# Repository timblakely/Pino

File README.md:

# Pino

Pino the robot. An ongoing project to build a quadrupedal robot from the ground
up. 

## Disclaimer: this will not currently work for you.

This repository is a continuously changing, seething mess, and will continue to
be so for the forseeable future. I've made essentially zero effort to make this
work for anyone other than my own development environment, and the git commit
history is an absolute trainwreck. You're welcome to browse around the code, but
please don't expect anything to actually work without somewhat extensive removal
of the various hard-coded paths, hacks, and general terrible code health. If
you're still reading this and are actually interested in getting any of this to
_maybe_ compile, let me know via GitHub or my-github-username@gmail :)

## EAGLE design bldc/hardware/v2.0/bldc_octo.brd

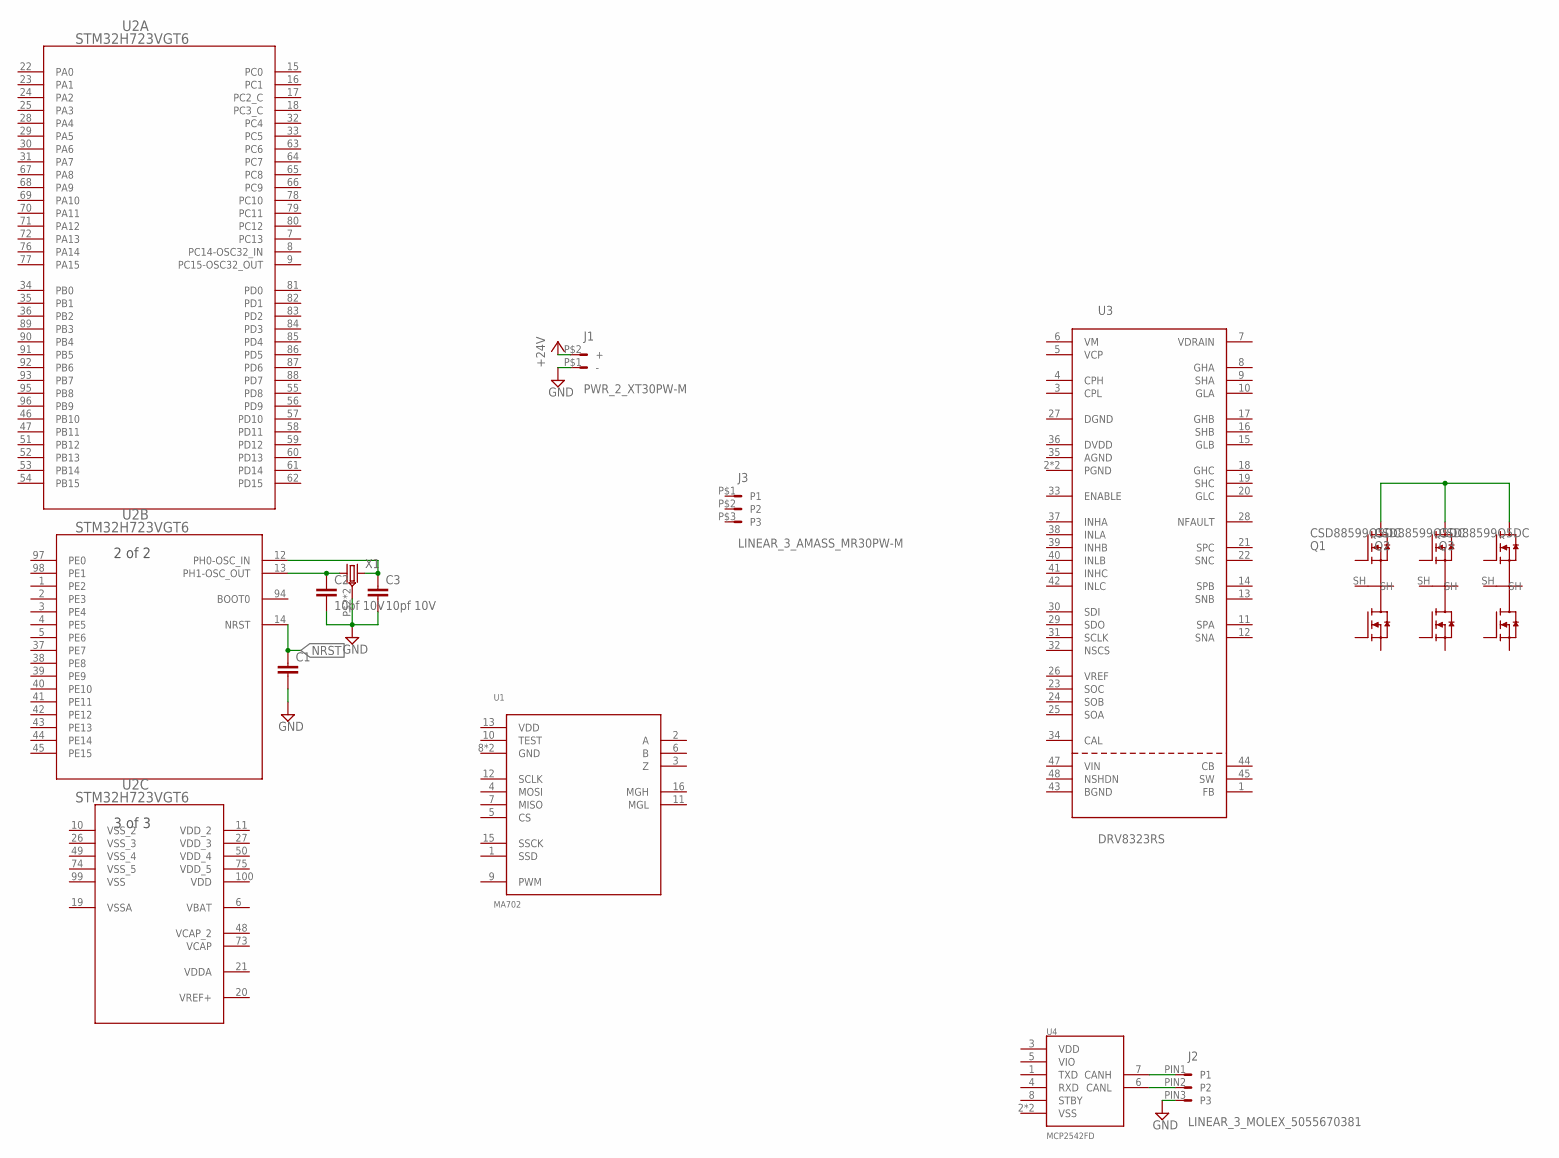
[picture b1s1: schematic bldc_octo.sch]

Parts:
C1: C0603
C2, C3: 10pf 10V; C0603
J1: PWR_2_XT30PW-M; XT30PW-M
J2: LINEAR_3_MOLEX_5055670381; MOLEX_5055670381
J3: LINEAR_3_AMASS_MR30PW-M; MR30PW-M
Q1, Q2, Q3: CSD88599Q5DC
U1: MA702; QFN-16_3X3
U2: STM32H723VGT6; LQFP100_STM
U3: DRV8323RS; VQFN-48_7X7
U4: MCP2542FD; TDFN_2X3
X1: CRYSTAL_NX2016SA-24MHZ-EXS00A-CS11335; NX201SA

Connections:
+24V: J1.P$2 (+)
GND: C1.2, C2.2, C3.2, J1.P$1 (-), J2.PIN3 (P3), X1.P$2 (GND), X1.P$4 (GND)
unnamed: J2.PIN1 (P1), U4.7 (CANH)
unnamed: J2.PIN2 (P2), U4.6 (CANL)
unnamed: C2.1, U2.13 (PH1-OSC_OUT), X1.P$1 (1)
unnamed: C3.1, U2.12 (PH0-OSC_IN), X1.P$3 (2)
unnamed: Q1.VIN$1 (V_IN), Q1.VIN$2 (V_IN), Q1.VIN$3 (V_IN), Q1.VIN$4 (V_IN), Q1.VIN$5 (V_IN), Q1.VIN$6 (V_IN), Q1.VIN$7 (V_IN), Q1.VIN$8 (V_IN), Q1.VIN$9 (V_IN), Q1.VIN$10 (V_IN), Q1.VIN$11 (V_IN), Q2.VIN$1 (V_IN), Q2.VIN$2 (V_IN), Q2.VIN$3 (V_IN), Q2.VIN$4 (V_IN), Q2.VIN$5 (V_IN), Q2.VIN$6 (V_IN), Q2.VIN$7 (V_IN), Q2.VIN$8 (V_IN), Q2.VIN$9 (V_IN), Q2.VIN$10 (V_IN), Q2.VIN$11 (V_IN), Q3.VIN$1 (V_IN), Q3.VIN$2 (V_IN), Q3.VIN$3 (V_IN), Q3.VIN$4 (V_IN), Q3.VIN$5 (V_IN), Q3.VIN$6 (V_IN), Q3.VIN$7 (V_IN), Q3.VIN$8 (V_IN), Q3.VIN$9 (V_IN), Q3.VIN$10 (V_IN), Q3.VIN$11 (V_IN)
NRST: C1.1, U2.14 (NRST)
VBAT: U2.6 (VBAT)
VCAP: U2.73 (VCAP)
VCAP_2: U2.48 (VCAP_2)
VDD: U2.100 (VDD)
VDDA: U2.21 (VDDA)
VDD_2: U2.11 (VDD_2)
VDD_3: U2.27 (VDD_3)
VDD_4: U2.50 (VDD_4)
VDD_5: U2.75 (VDD_5)
VREF+: U2.20 (VREF+)
VSS: U2.99 (VSS)
VSSA: U2.19 (VSSA)
VSS_2: U2.10 (VSS_2)
VSS_3: U2.26 (VSS_3)
VSS_4: U2.49 (VSS_4)
VSS_5: U2.74 (VSS_5)

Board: 4 copper layers, 14 parts (5 on the bottom side), 7 nets, no tracks yet.

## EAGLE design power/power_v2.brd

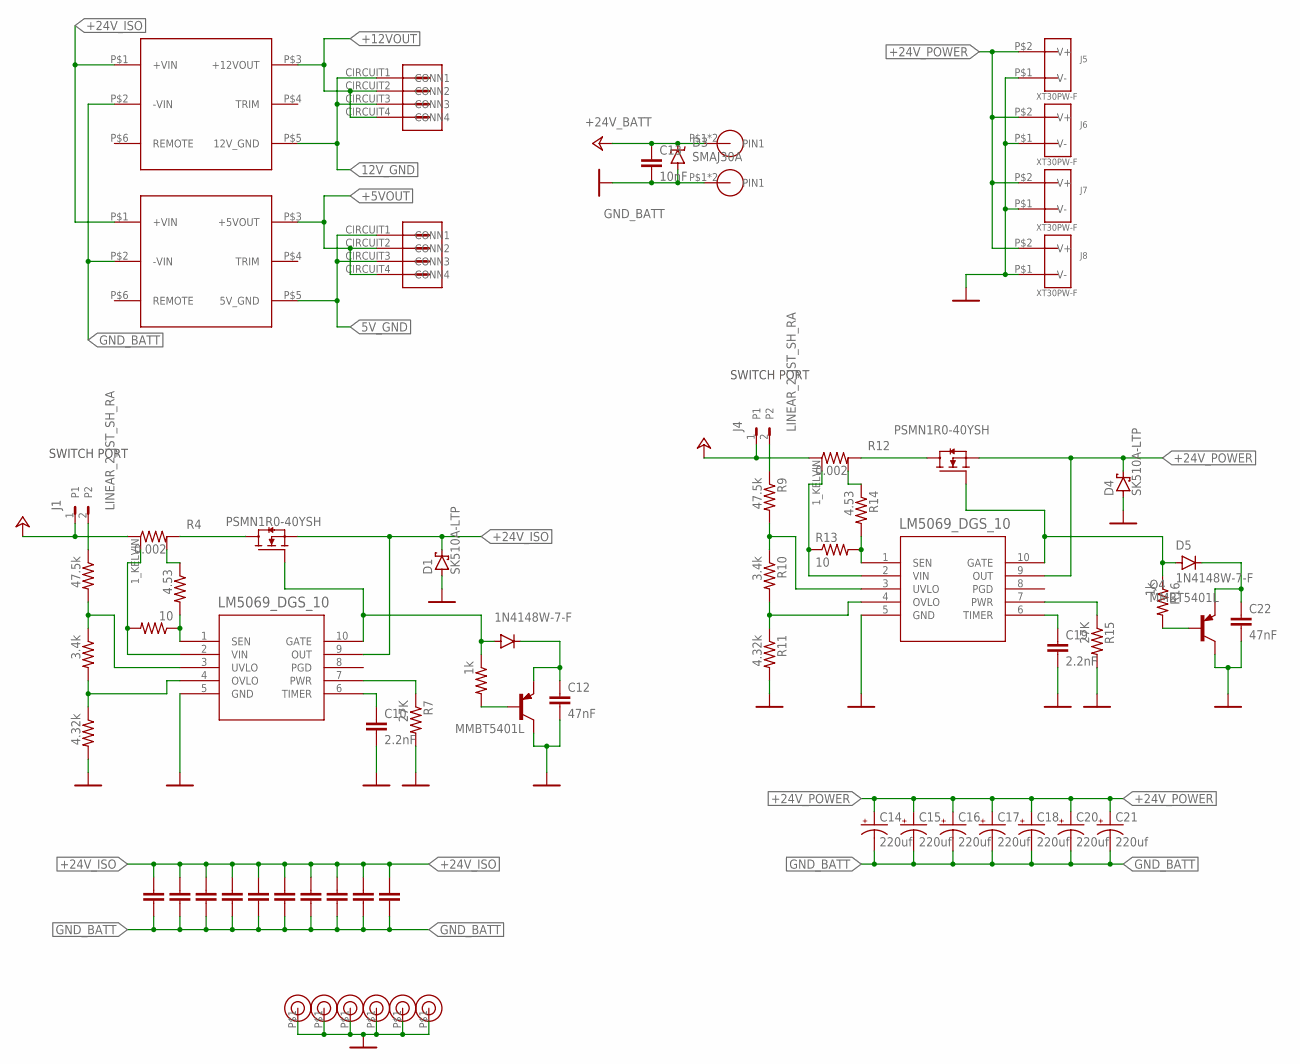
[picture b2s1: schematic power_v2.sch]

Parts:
C1: 2.2nF; C1210
C2, C3, C4, C5, C6, C7, C8, C9, C11: 10uF; C1210
C10, C19: 2.2nF; C0603
C12, C22: 47nF; C0603
C13: 10nF; C0603
C14, C15, C16, C17, C18, C20, C21: 220uf; C_ELEC_8X11_5
D1, D4: SK510A-LTP; DO-214AC
D2, D5: 1N4148W-7-F; SOD123
D3: SMAJ30A; DO-214AC
H1, H2, H3, H4, H5, H6: GND_HOLE_M3; HOLE_GND_M3
J1, J4: LINEAR_2_JST_SH_RA; JST_SM02B-SRSS-TB
J2: 12v; MOLEX_4_RA
J3: 5v; MOLEX_4_RA
J5, J6, J7, J8: XT30PW-F
P1, P2: FASTON1289_ST; FASTON_1289-ST
PS3: PDQ30-Q24-S12-D; PDQ30-D
PS4: PDQ30-Q24-S5-D; PDQ30-D
Q1, Q3: PSMN1R0-40YSH; LFPAK56E
Q2, Q4: MMBT5401L; SOT23-3
R1, R9: 47.5k; R0603
R2, R10: 3.4k; R0603
R3, R11: 4.32k; R0603
R4, R12: 0.002; R1210_KELVIN
R5, R13: 10; R0603
R6, R14: 4.53; R0603
R7, R15: 27K; R0603
R8, R16: 1k; R0603
U1, U2: LM5069_DGS_10; VSSOP_DGS_10

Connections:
5V_GND: J3.CIRCUIT1 (CONN1), J3.CIRCUIT3 (CONN3), PS4.P$5 (5V_GND)
12V_GND: J2.CIRCUIT1 (CONN1), J2.CIRCUIT3 (CONN3), PS3.P$5 (12V_GND)
+5VOUT: J3.CIRCUIT2 (CONN2), J3.CIRCUIT4 (CONN4), PS4.P$3 (+5VOUT)
+12VOUT: J2.CIRCUIT2 (CONN2), J2.CIRCUIT4 (CONN4), PS3.P$3 (+12VOUT)
+24V_BATT: C13.1, D3.C, J1.1, J4.1, P1.P$1, P1.P$2, R4.1A (1), R4.1B (1), R12.1A (1), R12.1B (1)
+24V_ISO: C1.1, C2.1, C3.1, C4.1, C5.1, C6.1, C7.1, C8.1, C9.1, C11.1, D1.C, PS3.P$1 (+VIN), PS4.P$1 (+VIN), Q1.1 (S), Q1.2 (S), Q1.3 (S), U1.9 (OUT)
+24V_POWER: C14.1 (+), C15.1 (+), C16.1 (+), C17.1 (+), C18.1 (+), C20.1 (+), C21.1 (+), D4.C, J5.P$2 (V+), J6.P$2 (V+), J7.P$2 (V+), J8.P$2 (V+), Q3.1 (S), Q3.2 (S), Q3.3 (S), U2.9 (OUT)
GND_BATT: C1.2, C2.2, C3.2, C4.2, C5.2, C6.2, C7.2, C8.2, C9.2, C10.2, C11.2, C12.2, C13.2, C14.2 (-), C15.2 (-), C16.2 (-), C17.2 (-), C18.2 (-), C19.2, C20.2 (-), C21.2 (-), C22.2, D1.A, D3.A, D4.A, H1.P$1, H2.P$1, H3.P$1, H4.P$1, H5.P$1, H6.P$1, J5.P$1 (V-), J6.P$1 (V-), J7.P$1 (V-), J8.P$1 (V-), P2.P$1, P2.P$2, PS3.P$2 (-VIN), PS4.P$2 (-VIN), Q2.C, Q4.C, R3.2, R7.2, R11.2, R15.2, U1.5 (GND), U2.5 (GND)
MOSFET_DRAIN: Q3.5 (D), R12.2A (2), R12.2B (2)
MOSFET_DRAIN1: Q1.5 (D), R4.2A (2), R4.2B (2)
unnamed: R9.2, R10.1, U2.3 (UVLO)
unnamed: R10.2, R11.1, U2.4 (OVLO)
unnamed: J4.2, R9.1
unnamed: R1.2, R2.1, U1.3 (UVLO)
unnamed: D5.A, Q3.4 (G), R16.1, U2.10 (GATE)
unnamed: R15.1, U2.7 (PWR)
unnamed: C19.1, U2.6 (TIMER)
unnamed: C22.1, D5.C, Q4.E
unnamed: Q4.B, R16.2
unnamed: R13.2, R14.2, U2.1 (SEN)
unnamed: R12.2_KELVIN (2K), R14.1
unnamed: R2.2, R3.1, U1.4 (OVLO)
unnamed: J1.2, R1.1
unnamed: D2.A, Q1.4 (G), R8.1, U1.10 (GATE)
unnamed: R7.1, U1.7 (PWR)
unnamed: C10.1, U1.6 (TIMER)
unnamed: C12.1, D2.C, Q2.E
unnamed: Q2.B, R8.2
unnamed: R12.1_KELVIN (1K), R13.1, U2.2 (VIN)
unnamed: R5.1, R6.2, U1.1 (SEN)
unnamed: R4.2_KELVIN (2K), R6.1
unnamed: R4.1_KELVIN (1K), R5.2, U1.2 (VIN)

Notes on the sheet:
SWITCH PORT

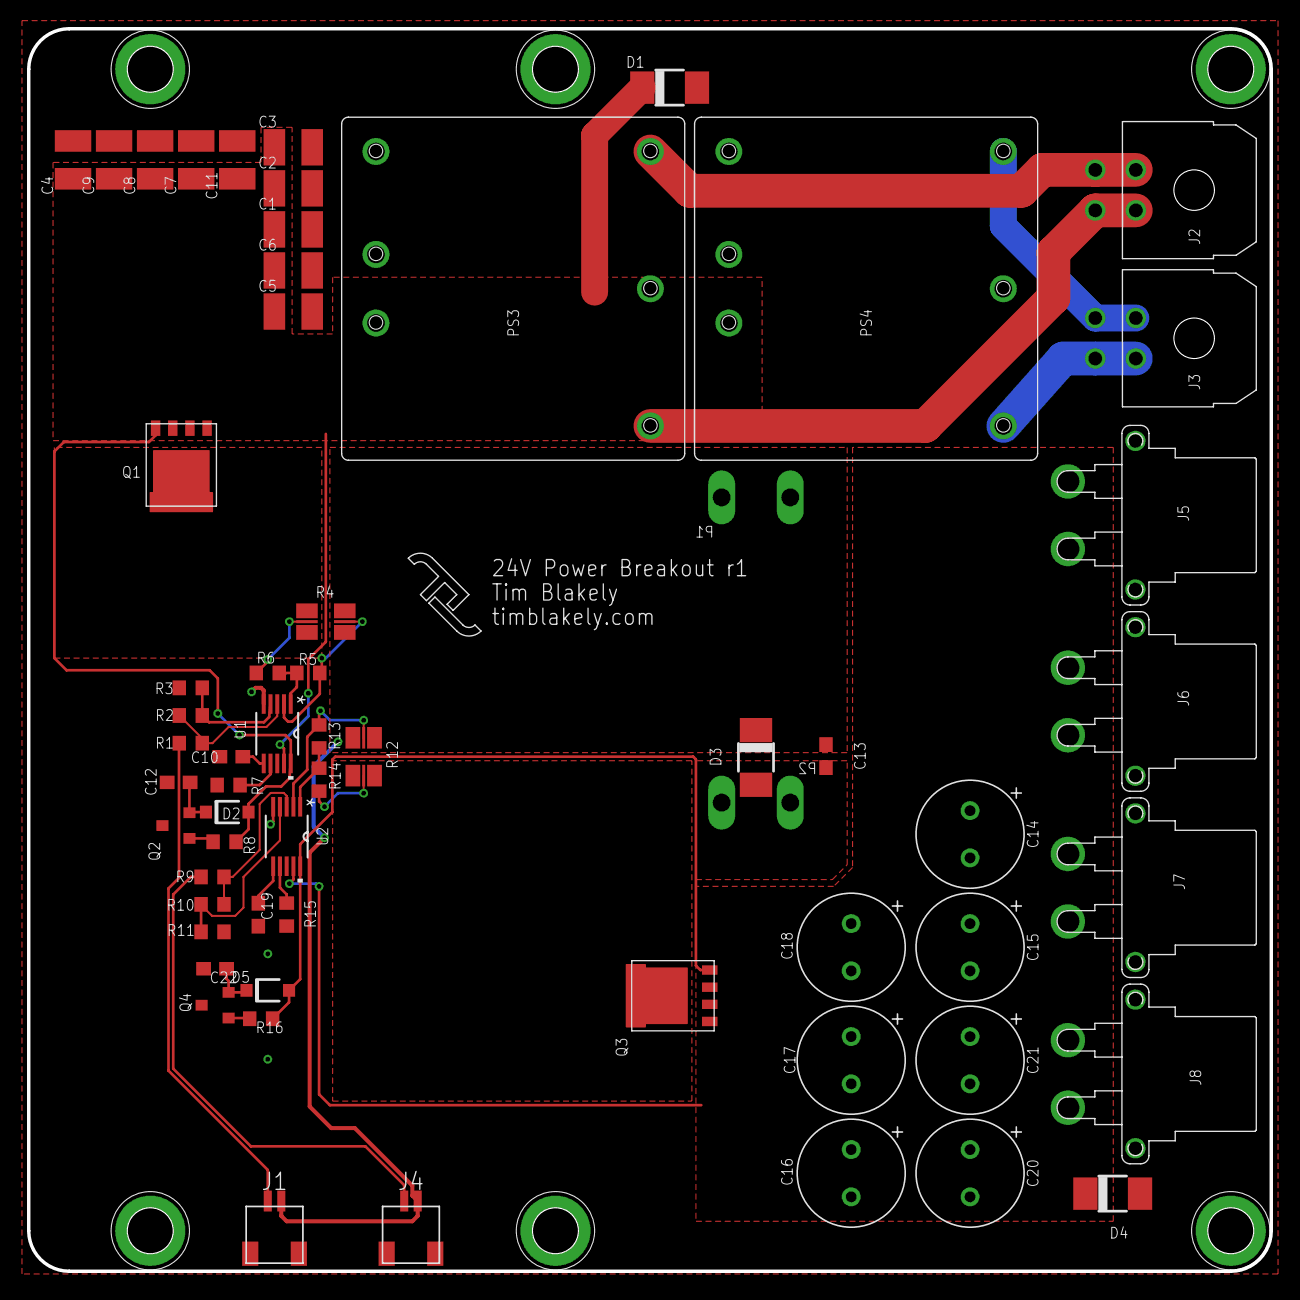
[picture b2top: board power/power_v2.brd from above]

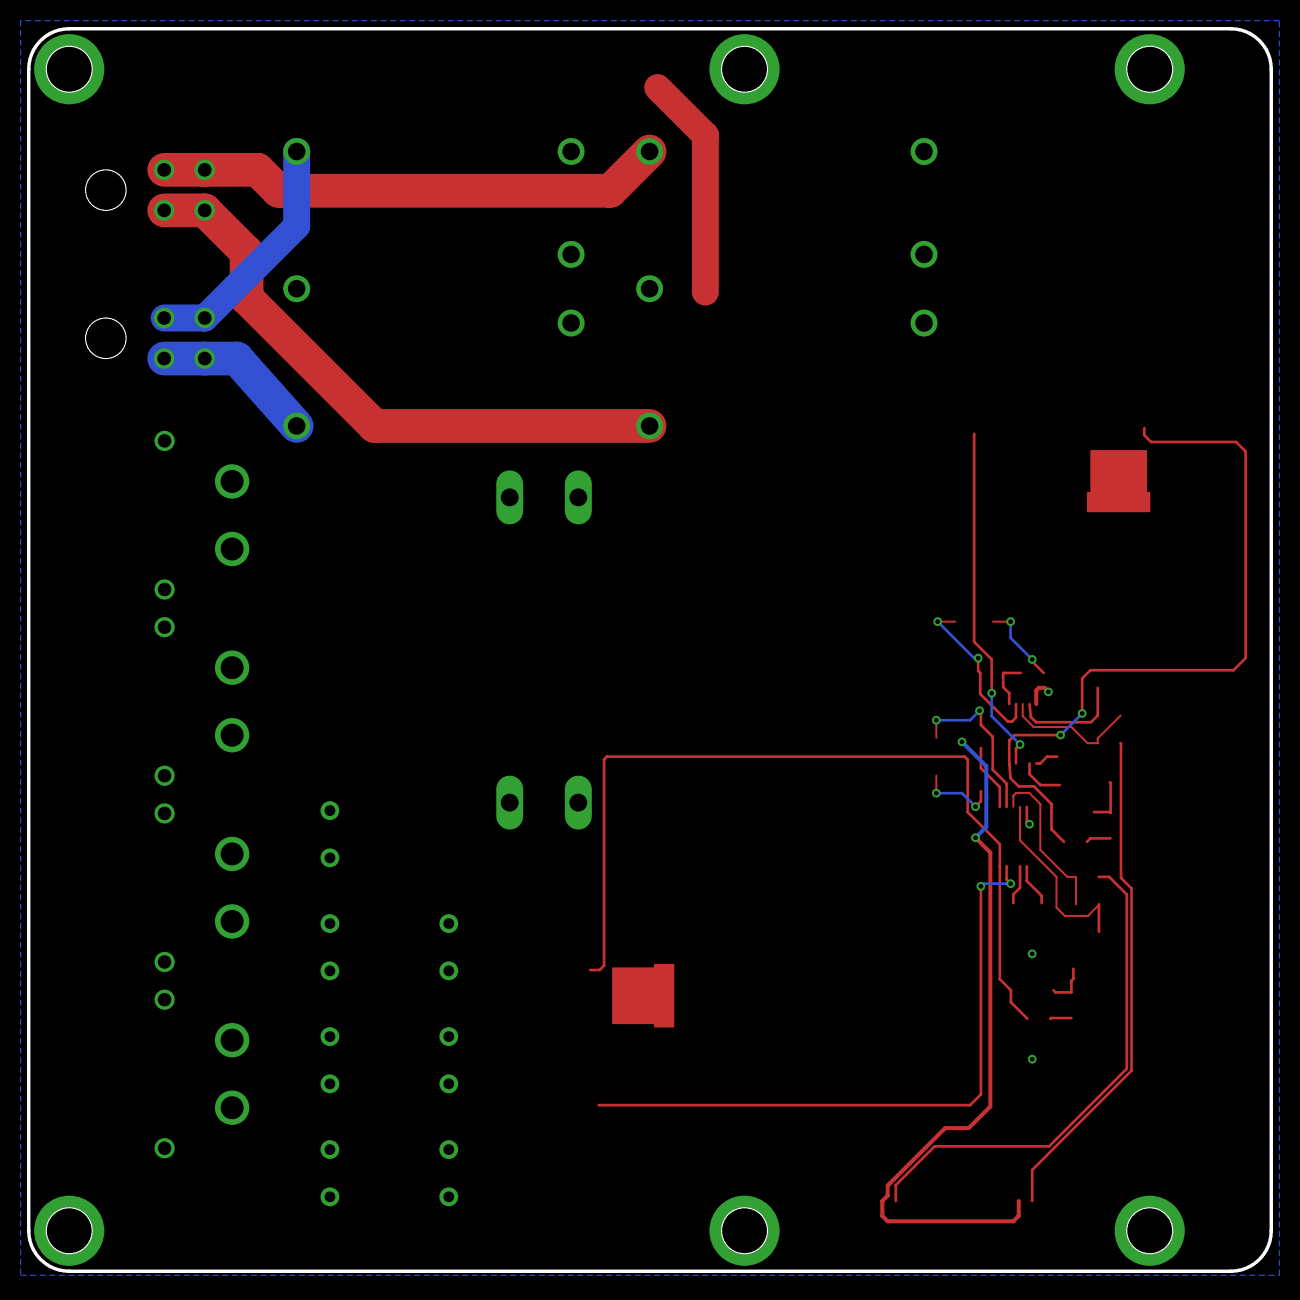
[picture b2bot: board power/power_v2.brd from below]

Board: 4 copper layers, 92.0 x 92.0 mm, 67 parts (2 on the bottom side), 32 nets.

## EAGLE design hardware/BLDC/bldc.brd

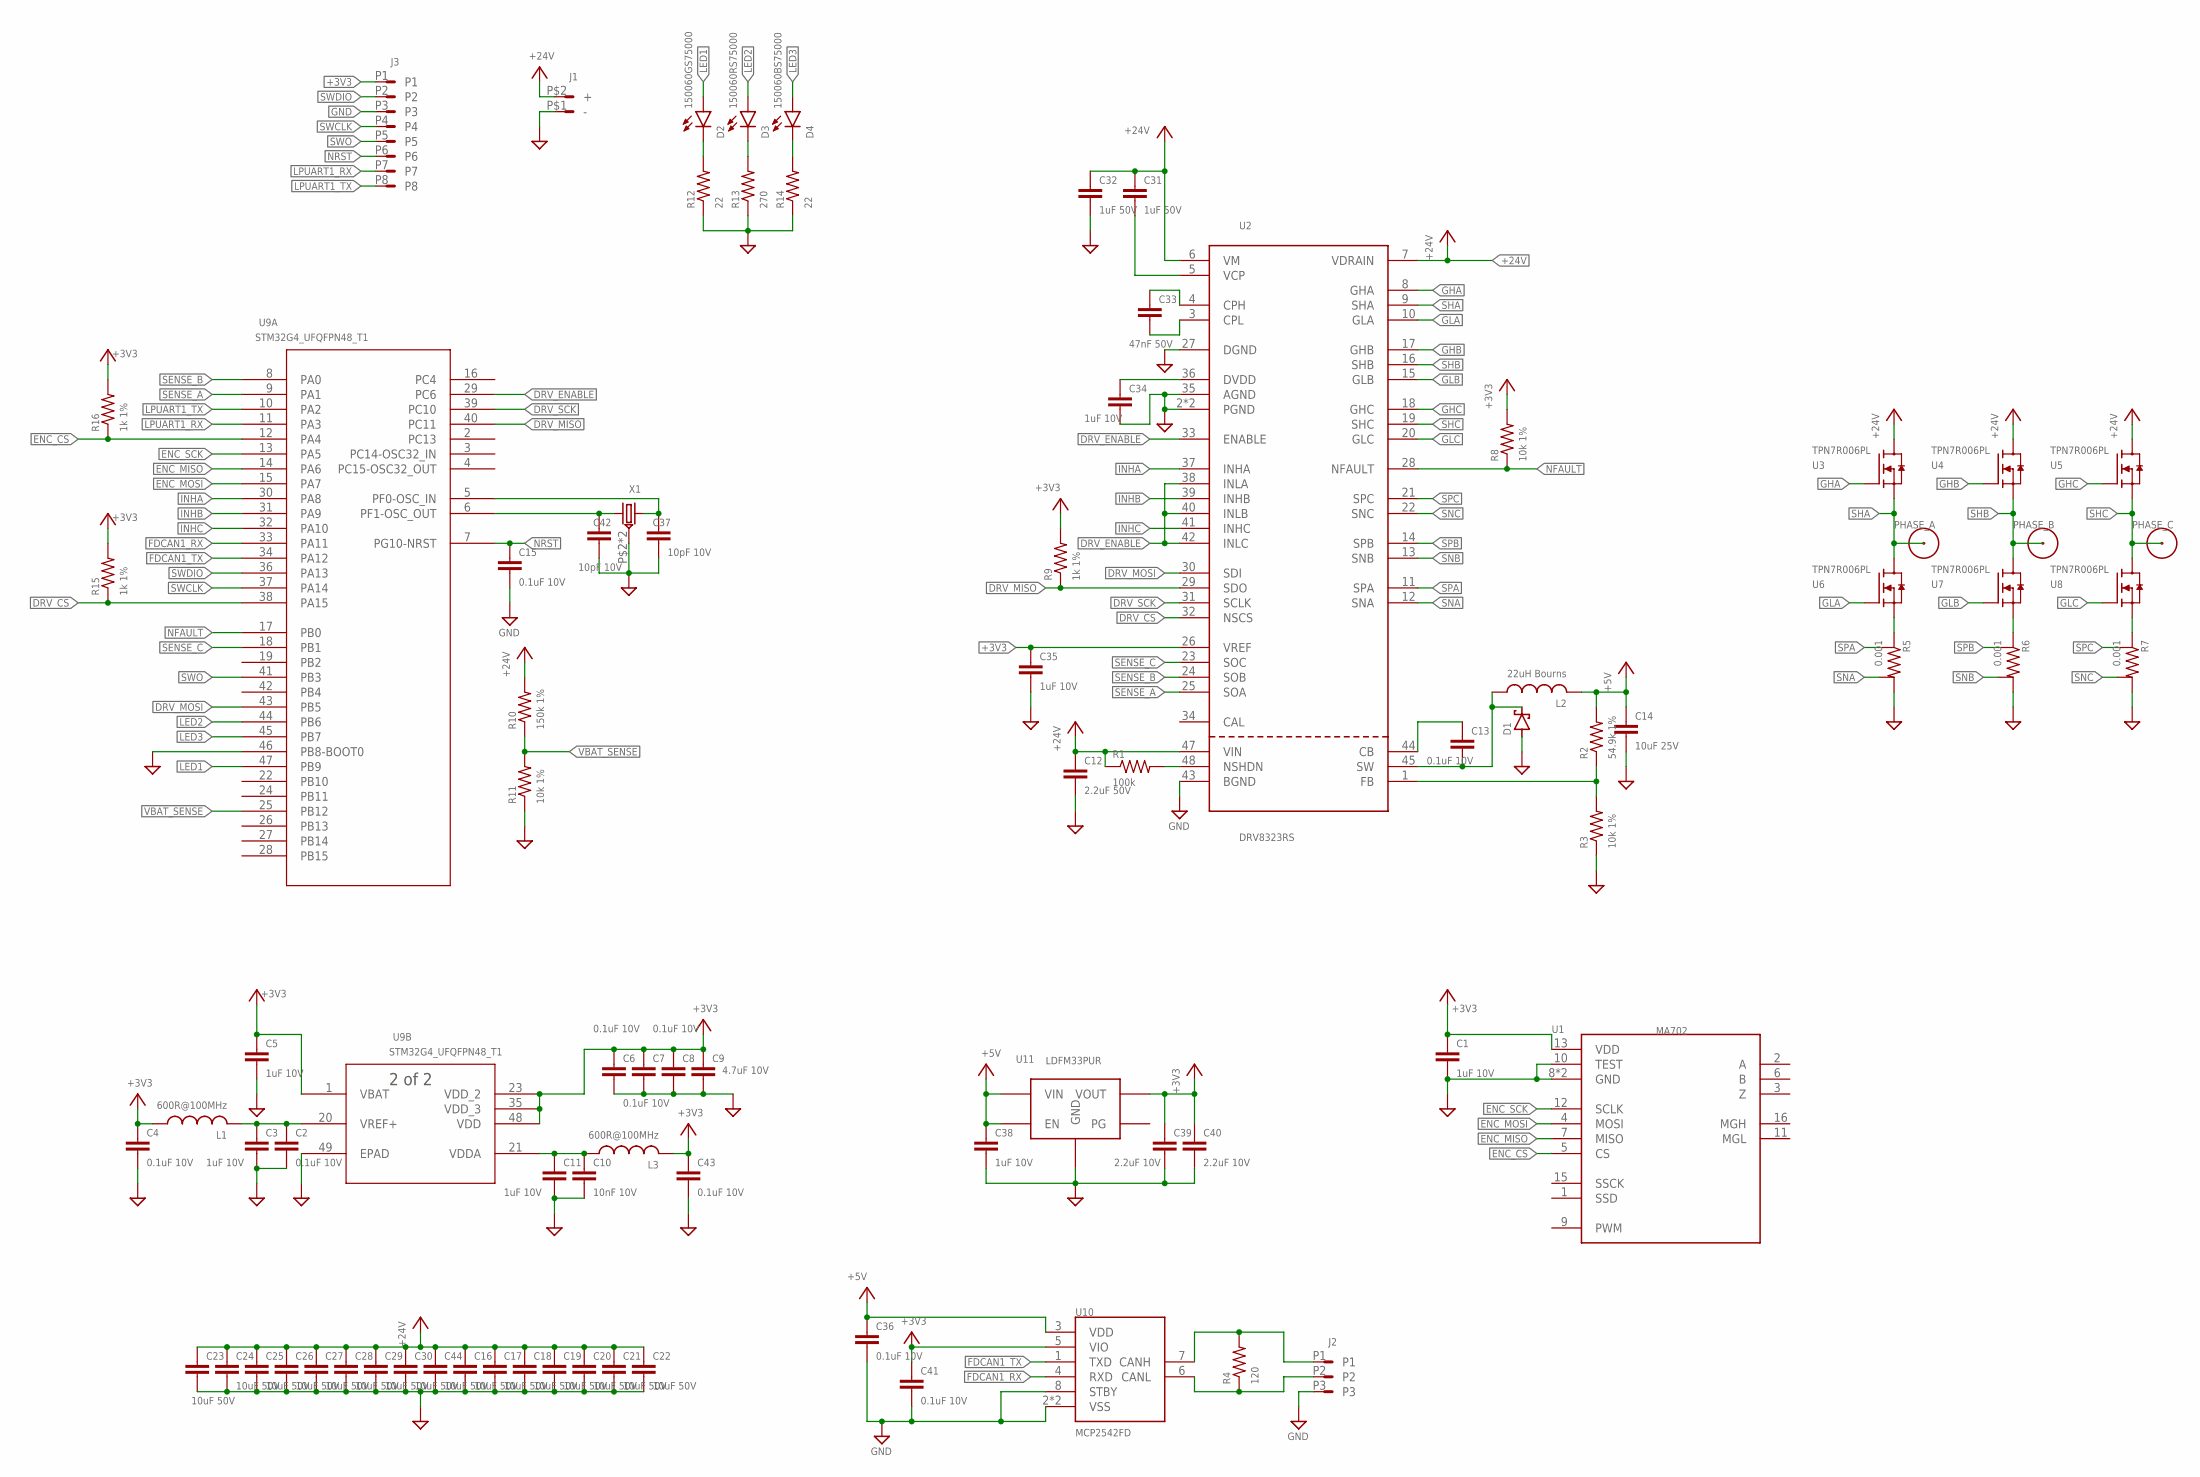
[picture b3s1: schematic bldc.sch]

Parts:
C1, C3, C5, C11, C34, C35, C38: 1uF 10V; C0402
C2, C4, C6, C7, C8, C13, C15, C36, C41, C43: 0.1uF 10V; C0402
C9: 4.7uF 10V; C0402
C10: 10nF 10V; C0402
C12: 2.2uF 50V; C0603
C14: 10uF 25V; C0603
C16, C17, C18, C19, C20, C21, C22, C23, C24, C25, C26, C27, C28, C29, C30, C44: 10uF 50V; C1206
C31, C32: 1uF 50V; C0603
C33: 47nF 50V; C0402
C37, C42: 10pF 10V; C0402
C39, C40: 2.2uF 10V; C0402
D1: SCHOTTKY_SOD123; SOD123
D2: 150060GS75000; D0603
D3: 150060RS75000; D0603
D4: 150060BS75000; D0603
J1: PWR_2_XT30PW-M; XT30PW-M
J2: LINEAR_35040500391; MOLEX_5040500391
J3: LINEAR_8530480810; MOLEX_530480810
L1, L3: 600R@100MHz; L0603
L2: 22uH Bourns; SDR0302
PHASE_A: WIRE_HOLE_AWG_18; AWG_18
PHASE_B: WIRE_HOLE_AWG_18; AWG_18
PHASE_C: WIRE_HOLE_AWG_18; AWG_18
R1: 100k; R0402
R2: 54.9k 1%; R0402
R3, R8, R11: 10k 1%; R0402
R4: 120; R0402
R5, R6, R7: 0.001; R1210_KELVIN
R9, R15, R16: 1k 1%; R0402
R10: 150k 1%; R0402
R12, R14: 22; R0402
R13: 270; R0402
U1: MA702; QFN-16_3X3
U2: DRV8323RS; VQFN-48_7X7
U3, U4, U5, U6, U7, U8: TPN7R006PL; 2-3X1S-TSONADVANCE
U9: STM32G4_UFQFPN48_T1; UFQFPN-48_7X7X0P55MM
U10: MCP2542FD; TDFN_2X3
U11: LDFM33PUR; DFN6_2X2
X1: CRYSTAL_NX2016SA-24MHZ-EXS00A-CS11335; NX201SA

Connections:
3.3V30MA: C34.1, U2.36 (DVDD)
+3V3: C1.1, C4.1, C5.1, C6.1, C7.1, C8.1, C9.1, C35.1, C39.1, C40.1, C41.1, C43.1, J3.P1, L1.1, L3.2, R8.2, R9.2, R15.2, R16.2, U1.13 (VDD), U2.26 (VREF), U9.1 (VBAT), U9.23 (VDD_2), U9.35 (VDD_3), U9.48 (VDD), U10.5 (VIO), U11.PIN1 (VOUT)
+5V: C14.1, C36.1, C38.1, L2.PIN2 (2), R2.2, U10.3 (VDD), U11.PIN5 (EN), U11.PIN6 (VIN)
+24V: C12.1, C16.1, C17.1, C18.1, C19.1, C20.1, C21.1, C22.1, C23.1, C24.1, C25.1, C26.1, C27.1, C28.1, C29.1, C30.1, C31.1, C32.1, C44.1, J1.P$2 (+), R1.1, R10.2, U2.6 (VM), U2.7 (VDRAIN), U2.47 (VIN), U3.DRAIN (D), U4.DRAIN (D), U5.DRAIN (D)
DRV_CS: R15.1, U2.32 (NSCS), U9.38 (PA15)
DRV_ENABLE: U2.33 (ENABLE), U2.38 (INLA), U2.40 (INLB), U2.42 (INLC), U9.29 (PC6)
DRV_MISO: R9.1, U2.29 (SDO), U9.40 (PC11)
DRV_MOSI: U2.30 (SDI), U9.43 (PB5)
DRV_SCK: U2.31 (SCLK), U9.39 (PC10)
ENC_CS: R16.1, U1.5 (CS), U9.12 (PA4)
ENC_MISO: U1.7 (MISO), U9.14 (PA6)
ENC_MOSI: U1.4 (MOSI), U9.15 (PA7)
ENC_SCK: U1.12 (SCLK), U9.13 (PA5)
FDCAN1_RX: U9.33 (PA11), U10.4 (RXD)
FDCAN1_TX: U9.34 (PA12), U10.1 (TXD)
GHA: U2.8 (GHA), U3.GATE (G)
GHB: U2.17 (GHB), U4.GATE (G)
GHC: U2.18 (GHC), U5.GATE (G)
GLA: U2.10 (GLA), U6.GATE (G)
GLB: U2.15 (GLB), U7.GATE (G)
GLC: U2.20 (GLC), U8.GATE (G)
GND: C1.2, C2.2, C3.2, C4.2, C5.2, C6.2, C7.2, C8.2, C9.2, C10.2, C11.2, C12.2, C14.2, C15.2, C16.2, C17.2, C18.2, C19.2, C20.2, C21.2, C22.2, C23.2, C24.2, C25.2, C26.2, C27.2, C28.2, C29.2, C30.2, C32.2, C34.2, C35.2, C36.2, C37.2, C38.2, C39.2, C40.2, C41.2, C42.2, C43.2, C44.2, D1.A, J1.P$1 (-), J2.P3, J3.P3, R3.1, R5.2A (2), R5.2B (2), R6.2A (2), R6.2B (2), R7.2A (2), R7.2B (2), R11.1, R12.1, R13.1, R14.1, U1.8 (GND), U1.10 (TEST), U1.PAD (GND), U2.2 (PGND), U2.27 (DGND), U2.35 (AGND), U2.43 (BGND), U2.PAD (PGND), U9.46 (PB8-BOOT0), U9.49 (EPAD), U10.2 (VSS), U10.8 (STBY), U10.PAD (VSS), U11.PAD (GND), U11.PIN4 (GND), X1.P$2 (GND), X1.P$4 (GND)
INHA: U2.37 (INHA), U9.30 (PA8)
INHB: U2.39 (INHB), U9.31 (PA9)
INHC: U2.41 (INHC), U9.32 (PA10)
LED1: D2.2 (A), U9.47 (PB9)
LED2: D3.2 (A), U9.44 (PB6)
LED3: D4.2 (A), U9.45 (PB7)
LPUART1_RX: J3.P7, U9.11 (PA3)
LPUART1_TX: J3.P8, U9.10 (PA2)
unnamed: C2.1, C3.1, L1.2, U9.20 (VREF+)
unnamed: C37.1, U9.5 (PF0-OSC_IN), X1.P$3 (2)
unnamed: C42.1, U9.6 (PF1-OSC_OUT), X1.P$1 (1)
unnamed: D4.1 (C), R14.2
unnamed: R1.2, U2.48 (NSHDN)
unnamed: C13.1, U2.44 (CB)
unnamed: D3.1 (C), R13.2
unnamed: C13.2, D1.C, L2.PIN1 (1), U2.45 (SW)
unnamed: R2.1, R3.2, U2.1 (FB)
unnamed: D2.1 (C), R12.2
unnamed: J2.P1, R4.2, U10.7 (CANH)
unnamed: J2.P2, R4.1, U10.6 (CANL)
unnamed: C31.2, U2.5 (VCP)
unnamed: C33.1, U2.4 (CPH)
unnamed: C33.2, U2.3 (CPL)
unnamed: C10.1, C11.1, L3.1, U9.21 (VDDA)
unnamed: R7.1A (1), R7.1B (1), U8.SOURCE (S), U8.SOURCE@1 (S), U8.SOURCE@2 (S)
unnamed: R6.1A (1), R6.1B (1), U7.SOURCE (S), U7.SOURCE@1 (S), U7.SOURCE@2 (S)
unnamed: R5.1A (1), R5.1B (1), U6.SOURCE (S), U6.SOURCE@1 (S), U6.SOURCE@2 (S)
NFAULT: R8.1, U2.28 (NFAULT), U9.17 (PB0)
NRST: C15.1, J3.P6, U9.7 (PG10-NRST)
SENSE_A: U2.25 (SOA), U9.9 (PA1)
SENSE_B: U2.24 (SOB), U9.8 (PA0)
SENSE_C: U2.23 (SOC), U9.18 (PB1)
SHA: PHASE_A.PIN1, U2.9 (SHA), U3.SOURCE (S), U3.SOURCE@1 (S), U3.SOURCE@2 (S), U6.DRAIN (D)
SHB: PHASE_B.PIN1, U2.16 (SHB), U4.SOURCE (S), U4.SOURCE@1 (S), U4.SOURCE@2 (S), U7.DRAIN (D)
SHC: PHASE_C.PIN1, U2.19 (SHC), U5.SOURCE (S), U5.SOURCE@1 (S), U5.SOURCE@2 (S), U8.DRAIN (D)
SNA: R5.2_KELVIN (K2), U2.12 (SNA)
SNB: R6.2_KELVIN (K2), U2.13 (SNB)
SNC: R7.2_KELVIN (K2), U2.22 (SNC)
SPA: R5.1_KELVIN (K1), U2.11 (SPA)
SPB: R6.1_KELVIN (K1), U2.14 (SPB)
SPC: R7.1_KELVIN (K1), U2.21 (SPC)
SWCLK: J3.P4, U9.37 (PA14)
SWDIO: J3.P2, U9.36 (PA13)
SWO: J3.P5, U9.41 (PB3)
VBAT_SENSE: R10.1, R11.2, U9.25 (PB12)

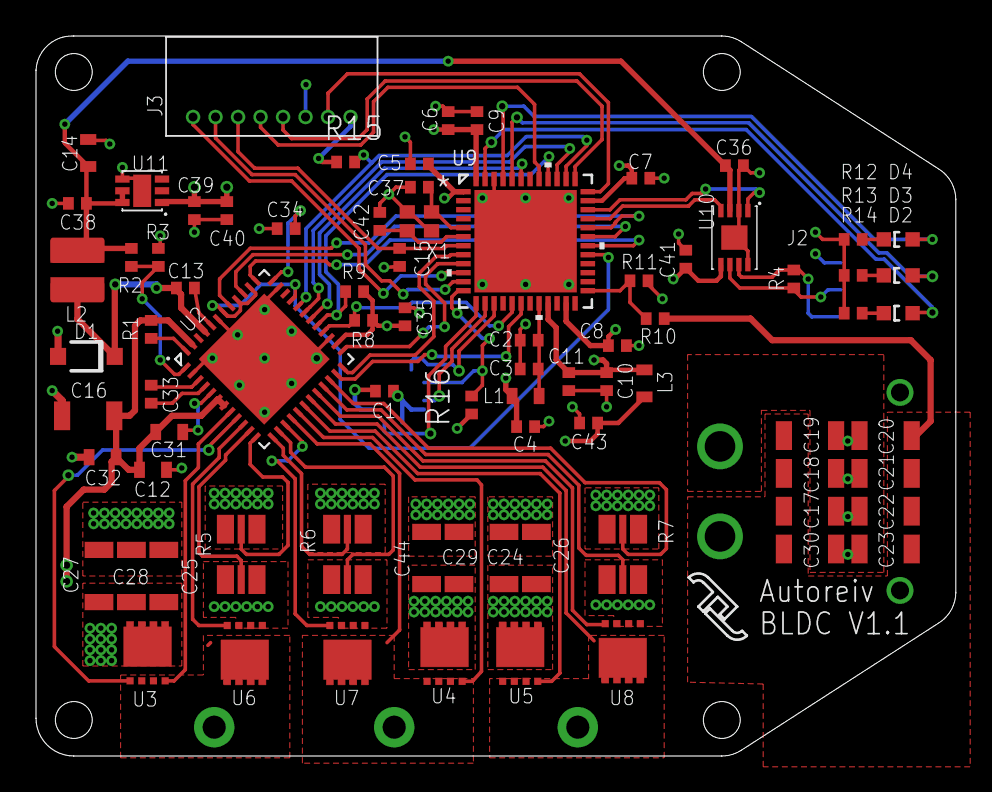
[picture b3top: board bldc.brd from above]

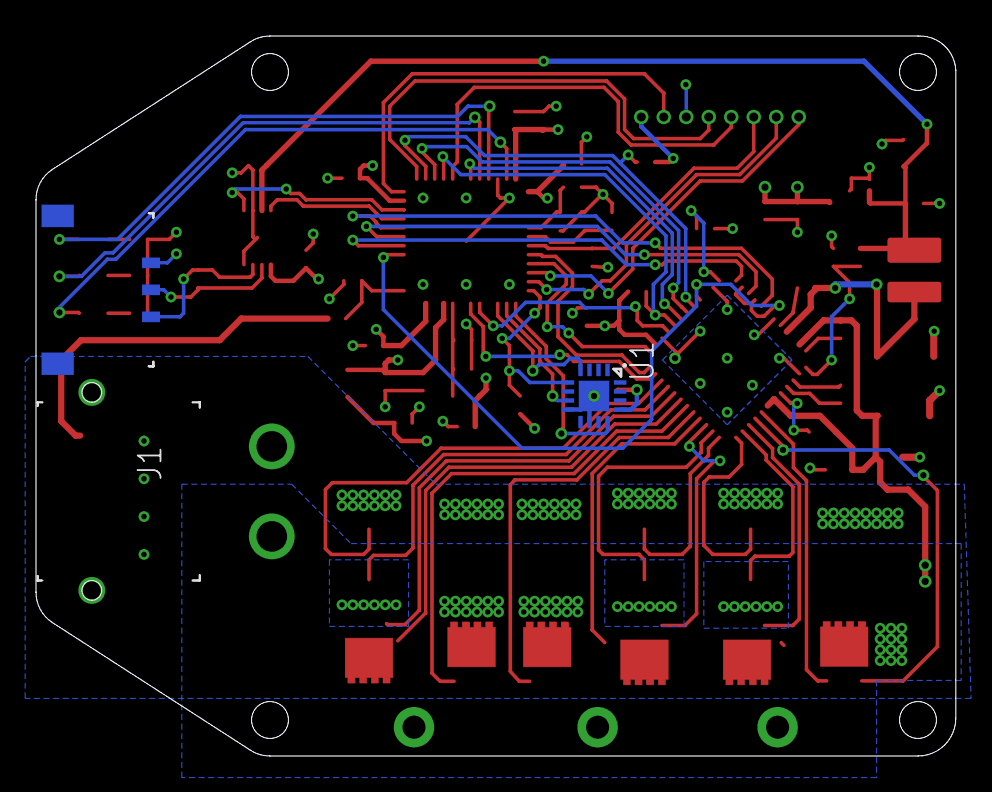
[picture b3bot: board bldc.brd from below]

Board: 4 copper layers, 51.1 x 40.0 mm, 85 parts (3 on the bottom side), 67 nets.

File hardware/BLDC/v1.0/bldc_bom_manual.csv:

Qty,Value,Device,Package,Parts,Part no
3,0.001,R_SENSE_1210,R1210_KELVIN,"R5, R6, R7",PMR25HZPFV1L00
10,0.1uF 10V,C0402,C0402,"C2, C4, C6, C7, C8, C13, C15, C36, C41, C43",LMK105BJ104KV-F
1,100k,R0402,R0402,R1,RC0402FR-07100KL
4,10k 1%,R0402,R0402,"R3, R8, R9, R11",RC0402FR-0710KL
1,10nF 10V,C0402,C0402,C10,885012005007
1,10uF 25V,C0603,C0603,C14,GRM188R61E106MA73D
16,10uF 50V,C1206,C1206,"C16, C17, C18, C19, C20, C21, C22, C23, C24, C25, C26, C27, C28, C29, C30, C44",GRT31CR61H106ME01L
1,120,R0402,R0402,R4,RK73H1ETTP1200F
1,150060BS75000,LED_0603,D0603,D4,150060BS75000
1,150060GS75000,LED_0603,D0603,D2,150060GS75000
1,150060RS75000,LED_0603,D0603,D3,150060RS75000
1,150k 1%,R0402,R0402,R10,RC0402FR-07150KL
7,1uF 10V,C0402,C0402,"C1, C3, C5, C11, C34, C35, C38",GRM155R71A104KA01D
2,1uF 50V,C0603,C0603,"C31, C32",GRT188R61H105KE13D
2,2.2uF 10V,C0402,C0402,"C39, C40",GRM155R61A225KE95D
1,2.2uF 50V,C0603,C0603,C12,GRM188R61H225KE11D
2,22,R0402,R0402,"R12, R14",RC0402FR-0722RL
1,22uH Bourns,L_SDR0302,SDR0302,L2,SDR0302-220ML
1,270,R0402,R0402,R13,ERJ-2RKF2700X
1,4.7uF 10V,C0402,C0402,C9,GRM155R61A475MEAAD
1,47nF 50V,C0402,C0402,C33,GCM155R71H472KA37D
1,54.9k 1%,R0402,R0402,R2,RC0402FR-0754K9L
2,6.8pF 10V,C0402,C0402,"C37, C42",885012005007
2,600R@100MHz,DC_CHOKE_FERRITE_BEAD_0603,L0603,"L1, L3",BLM18KG601SN1D
1,CRYSTAL_NX2016SA-24MHZ-EXS00A-CS11335,CRYSTAL_NX2016SA-24MHZ-EXS00A-CS11335,NX201SA,X1,NX2016SA-24MHZ-EXS00A-CS11335
1,DRV8323RS,DRV8323RS,VQFN-48_7X7,U2,DRV8323RSRGZR
1,LDFM33PUR,LDFM33PUR,DFN6_2X2,U11,LDFM33PUR
1,,,MOLEX_5040500391‎,J2,5040500391‎
1,,,MOLEX_5040500891‎,J3,5040500891‎
1,MA702,MA702,QFN-16_3X3,U1,MA702GQ-Z
1,MCP2542FD,MCP2542FD,TDFN_2X3,U10,MCP2542FDT-H/MNY
1,PWR_2_XT30PW-M,PWR_2_XT30PW-M,XT30PW-M,J1,
1,SCHOTTKY_SOD123,SCHOTTKY_SOD123,SOD123,D1,MBR0530T1G
1,STM32G4_UFQFPN48_T1,STM32G4_UFQFPN48_T1,UFQFPN-48_7X7X0P55MM,U9,STM32G474CEU6
6,TPN7R006PL,TPN7R006PL,2-3X1S-TSONADVANCE,"U3, U4, U5, U6, U7, U8","TPN7R006PL,L1Q"
3,WIRE_HOLE_AWG_18,WIRE_HOLE_AWG_18,AWG_18,"PHASE_A, PHASE_B, PHASE_C",

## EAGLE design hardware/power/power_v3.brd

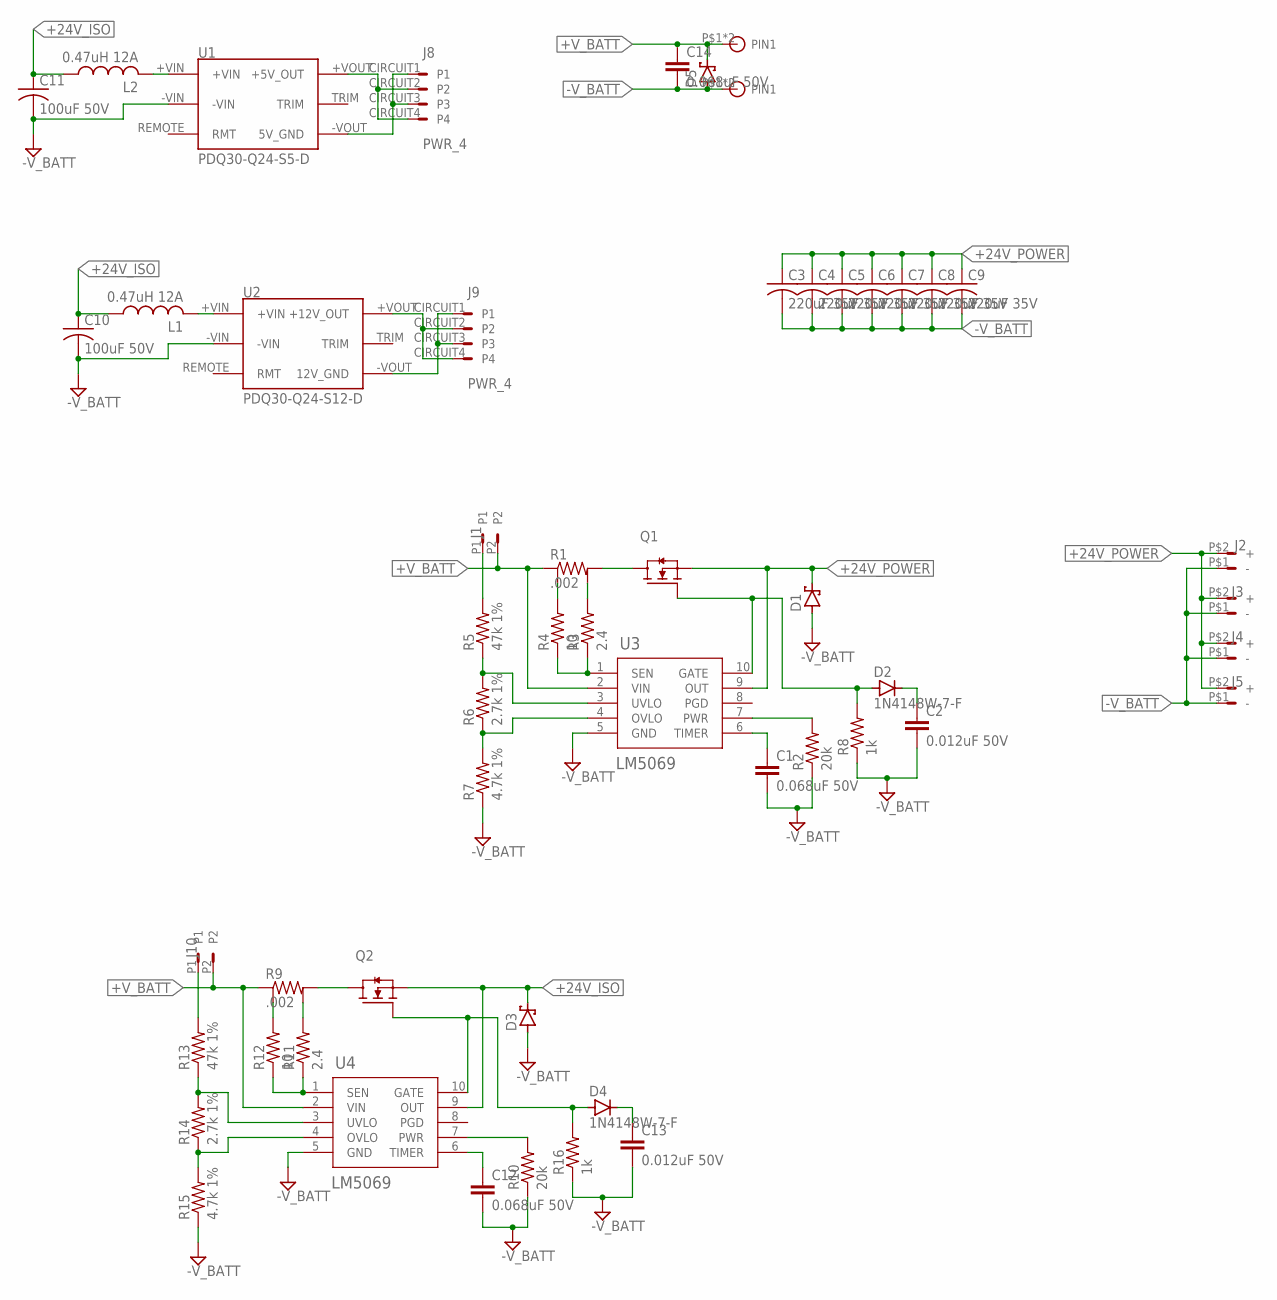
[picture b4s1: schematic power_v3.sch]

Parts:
C1, C12, C14: 0.068uF 50V; C0603
C2, C13: 0.012uF 50V; C0603
C3, C4, C5, C6, C7, C8, C9: 220uF 35V; C_POL_PANASONIC_F
C10, C11: 100uF 50V; C_POL_PANASONIC_F
D1, D3, D5: 5_0SMDJ24A; SOD123
D2, D4: 1N4148W-7-F; SOD123
J1, J10: LINEAR_2_5040500291; MOLEX_5040500291
J2, J3, J4, J5: PWR_2_XT30PW-F; XT30PW-F
J6, J7: FASTON; FASTON_1289-ST
J8, J9: PWR_4; MOLEX_4_RA
L1, L2: 0.47uH 12A; SRP5030TA
Q1, Q2: CSD19536KTT; TO-263
R1, R9: .002; R2512_KELVIN
R2, R10: 20k; R0603
R3, R11: 2.4; R0603
R4, R12: 10; R0603
R5, R13: 47k 1%; R0603
R6, R14: 2.7k 1%; R0603
R7, R15: 4.7k 1%; R0603
R8, R16: 1k; R0603
U1: PDQ30-Q24-S5-D; PDQ30-D
U2: PDQ30-Q24-S12-D; PDQ30-D
U3, U4: LM5069; VSSOP_10

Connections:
5V_GND: J8.CIRCUIT1 (P1), J8.CIRCUIT3 (P3), U1.-VOUT (5V_GND)
12V_GND: J9.CIRCUIT1 (P1), J9.CIRCUIT3 (P3), U2.-VOUT (12V_GND)
+5V: J8.CIRCUIT2 (P2), J8.CIRCUIT4 (P4), U1.+VOUT (+5V_OUT)
+12V: J9.CIRCUIT2 (P2), J9.CIRCUIT4 (P4), U2.+VOUT (+12V_OUT)
+24V_ISO: C10.POS, C11.POS, D3.C, L1.P$1 (1), L2.P$1 (1), Q2.3 (S), U4.9 (OUT)
+24V_POWER: C3.POS, C4.POS, C5.POS, C6.POS, C7.POS, C8.POS, C9.POS, D1.C, J2.P$2 (+), J3.P$2 (+), J4.P$2 (+), J5.P$2 (+), Q1.3 (S), U3.9 (OUT)
+V_BATT: C14.1, D5.C, J1.P2, J6.P$1, J6.P$2, J10.P2, R1.1A (1), R1.1B (1), R9.1A (1), R9.1B (1), U3.2 (VIN), U4.2 (VIN)
-V_BATT: C1.2, C2.2, C3.NEG, C4.NEG, C5.NEG, C6.NEG, C7.NEG, C8.NEG, C9.NEG, C10.NEG, C11.NEG, C12.2, C13.2, C14.2, D1.A, D3.A, D5.A, J2.P$1 (-), J3.P$1 (-), J4.P$1 (-), J5.P$1 (-), J7.P$1, J7.P$2, R2.1, R7.1, R8.1, R10.1, R15.1, R16.1, U1.-VIN, U2.-VIN, U3.5 (GND), U4.5 (GND)
unnamed: Q1.2 (D), R1.2A (2), R1.2B (2)
unnamed: D2.A, Q1.1 (G), R8.2, U3.10 (GATE)
unnamed: C1.1, U3.6 (TIMER)
unnamed: R2.2, U3.7 (PWR)
unnamed: R3.1, R4.1, U3.1 (SEN)
unnamed: R1.2_KELVIN (K2), R3.2
unnamed: J1.P1, R5.2
unnamed: R5.1, R6.2, U3.3 (UVLO)
unnamed: R6.1, R7.2, U3.4 (OVLO)
unnamed: R1.1_KELVIN (K1), R4.2
unnamed: C2.1, D2.C
unnamed: L1.P$2 (2), U2.+VIN
unnamed: L2.P$2 (2), U1.+VIN
unnamed: Q2.2 (D), R9.2A (2), R9.2B (2)
unnamed: C12.1, U4.6 (TIMER)
unnamed: R10.2, U4.7 (PWR)
unnamed: R11.1, R12.1, U4.1 (SEN)
unnamed: R9.2_KELVIN (K2), R11.2
unnamed: R13.1, R14.2, U4.3 (UVLO)
unnamed: R14.1, R15.2, U4.4 (OVLO)
unnamed: J10.P1, R13.2
unnamed: R9.1_KELVIN (K1), R12.2
unnamed: C13.1, D4.C
unnamed: D4.A, Q2.1 (G), R16.2, U4.10 (GATE)

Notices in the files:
parts and their libraries:
_T_ic: COPYRIGHT: Copyright (C) 2016 Accelerated Designs. All rights reserved
COPYRIGHT: Copyright (C) 2018 Accelerated Designs. All rights reserved
